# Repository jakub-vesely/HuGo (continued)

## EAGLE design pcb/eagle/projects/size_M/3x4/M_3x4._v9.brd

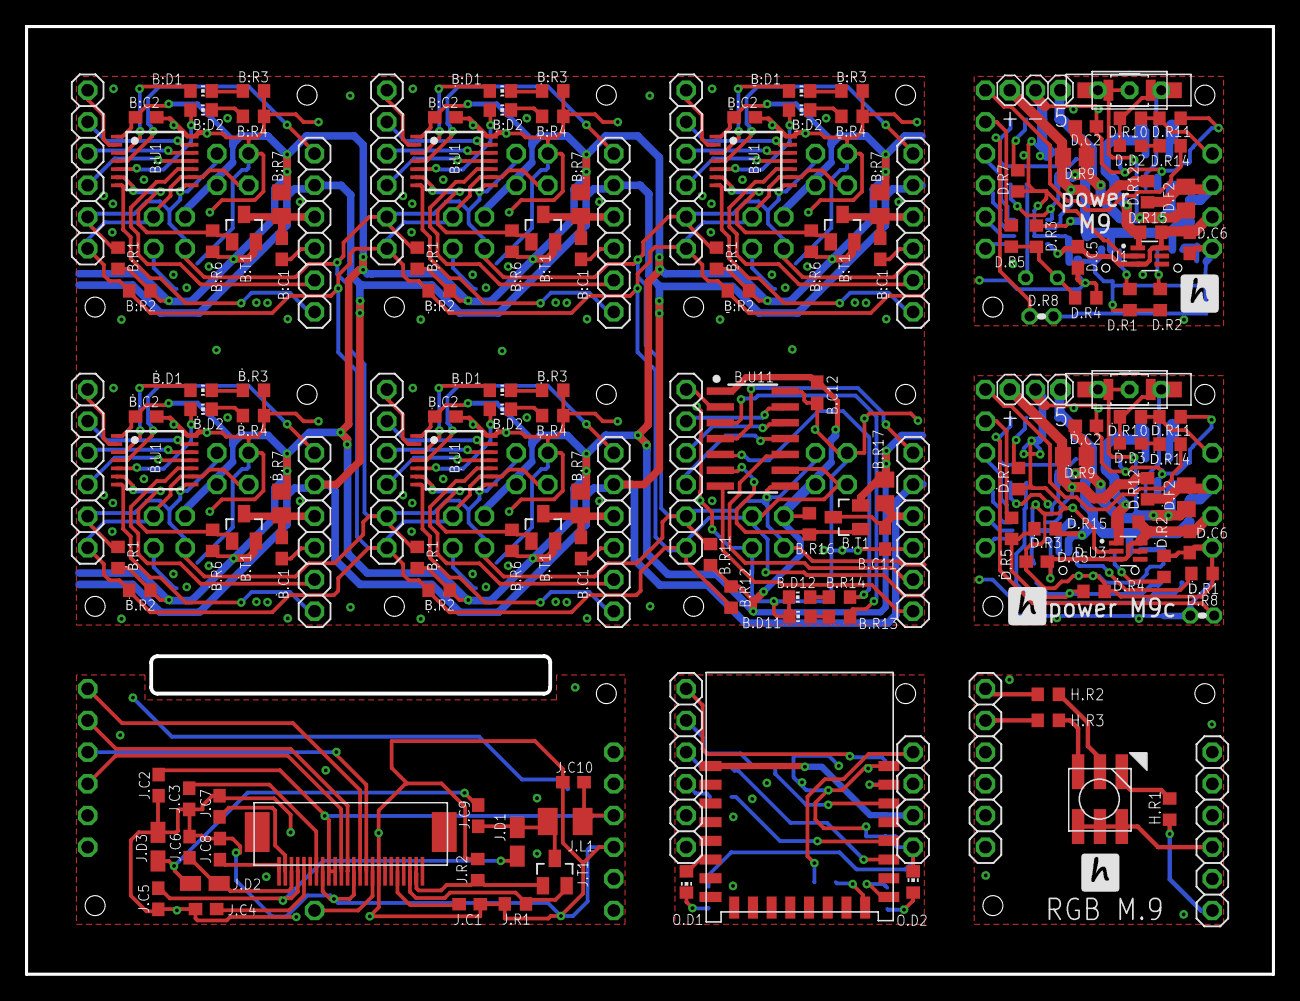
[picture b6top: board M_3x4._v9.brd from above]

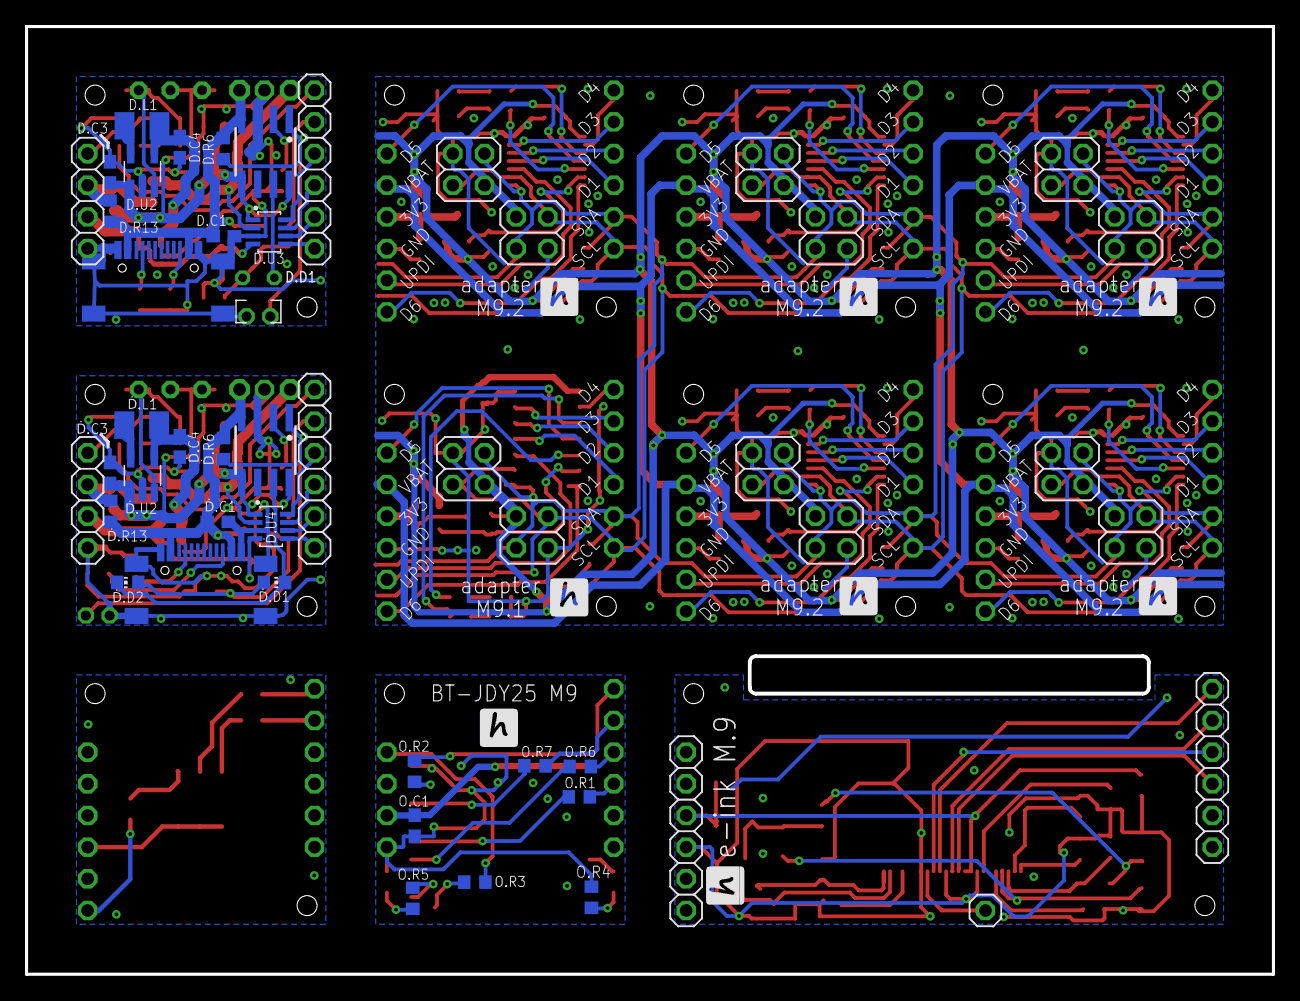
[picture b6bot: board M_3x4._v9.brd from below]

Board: 2 copper layers, 100.0 x 76.0 mm, 205 parts (50 on the bottom side), 170 nets.

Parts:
B.C11, B.C12: 100n; C0603
B.D11: RED; CHIP-LED0603
B.D12: GREEN; CHIP-LED0603
B.J1, B.J2, B.J5, B.J8, B.J9, B.J12, B.J13, B.J16, B.J17, B.J20, B.J21, B.J24: 1X06
B.J3, B.J4, B.J6, B.J7, B.J10, B.J11, B.J14, B.J15, B.J18, B.J19, B.J22, B.J23: 2X02
B.R11, B.R12, B.R14: 2k2; R0603
B.R13: 330; R0603
B.R16: 100k; R0603
B.R17: alt fuse or 0R; FUSE
B.T1: FDV304; SO23
B.U11: AT414; SO14
B:C1, B:C2: 100n; C0603
B:D1: RED; CHIP-LED0603
B:D2: GREEN; CHIP-LED0603
B:R1, B:R2, B:R4: 2k2; R0603
B:R3: 330; R0603
B:R6: 100k; R0603
B:R7: alt fuse or 0R; FUSE
B:T1: FDV304; SO23
B:U1: ATTINY3224-XU; TSSOP14
D.C1, D.C2, D.C3: 4u7; C0603
D.C4: 10u; C0603
D.C5, D.C6: 100n; C0603
D.D1: LED_1.8
D.D2: DIODE
D.F2: 1.1A; R0805
D.J2: 1X06
D.J3: 1X04
D.L1: 2u2; L3230M
D.LIPOL: PINHEAD-1X3-2; 1X-03-2
D.ON/OFF/RESET: SWITCH
D.R1, D.R2, D.R4: 5k1; R0603
D.R3: 3k3; R0603
D.R5, D.R6: 10k; R0603
D.R7: I=1800/R; R0603
D.R8: TERM_10K; THERM
D.R9: 0.1R; R0805
D.R10: 150k; R0603
D.R11: 330k; R0603
D.R12, D.R13: 0; R0603
D.R14: 680k; R0603
D.R15: 0R; R0603
D.U1: CN3083; SOP8
D.U2: LM3671_3.3; SOT32-5
D.U3: SOT23-8
G.J1: 1X06
G.J2: 1X04
H.D1: RGB_WW-FCE50TC-Q1
H.J1, H.J2: 1X06
H.R1, H.R2, H.R3: 82; R0603
J.C1, J.C4, J.C5, J.C6, J.C7, J.C9, J.C10: 4u7; C0603
J.C2, J.C3, J.C8: 1u; C0603
J.D1, J.D2, J.D3: SHOTKY_2.8
J.J1, J.J3: 1X06
J.J2: 1X01
J.J4: E-INK-24
J.L1: 10uH/1A; L3230M
J.R1: 82; R0603
J.R2: 100k; R0603
J.T1: NX3008; SO23
O.C1: 100n; C0603
O.D1, O.D2: CHIP-LED0603
O.R1, O.R2, O.R3, O.R4, O.R5, O.R6, O.R7: 2k2; R0603
U1: LM66100DCKR; SOT65P210X110-6N
U$1: USB-C
U$2: JDY-25
Ḃ.C1, Ḃ.C2: 100n; C0603
Ḃ.D1: RED; CHIP-LED0603
Ḃ.D2: GREEN; CHIP-LED0603
Ḃ.R1, Ḃ.R2, Ḃ.R4: 2k2; R0603
Ḃ.R3: 330; R0603
Ḃ.R6: 100k; R0603
Ḃ.R7: alt fuse or 0R; FUSE
Ḃ.T1: FDV304; SO23
Ḃ.U1: ATTINY3224-XU; TSSOP14
Ḅ.C1, Ḅ.C2: 100n; C0603
Ḅ.D1: RED; CHIP-LED0603
Ḅ.D2: GREEN; CHIP-LED0603
Ḅ.R1, Ḅ.R2, Ḅ.R4: 2k2; R0603
Ḅ.R3: 330; R0603
Ḅ.R6: 100k; R0603
Ḅ.R7: alt fuse or 0R; FUSE
Ḅ.T1: FDV304; SO23
Ḅ.U1: ATTINY3224-XU; TSSOP14
Ḅ:C1, Ḅ:C2: 100n; C0603
Ḅ:D1: RED; CHIP-LED0603
Ḅ:D2: GREEN; CHIP-LED0603
Ḅ:R1, Ḅ:R2, Ḅ:R4: 2k2; R0603
Ḅ:R3: 330; R0603
Ḅ:R6: 100k; R0603
Ḅ:R7: alt fuse or 0R; FUSE
Ḅ:T1: FDV304; SO23
Ḅ:U1: ATTINY3224-XU; TSSOP14
Ḇ:C1, Ḇ:C2: 100n; C0603
Ḇ:D1: RED; CHIP-LED0603
Ḇ:D2: GREEN; CHIP-LED0603
Ḇ:R1, Ḇ:R2, Ḇ:R4: 2k2; R0603
Ḇ:R3: 330; R0603
Ḇ:R6: 100k; R0603
Ḇ:R7: alt fuse or 0R; FUSE
Ḇ:T1: FDV304; SO23
Ḇ:U1: ATTINY3224-XU; TSSOP14
Ḋ.BTN: SWITCH
Ḋ.C1, Ḋ.C2, Ḋ.C3: 4u7; C0603
Ḋ.C4: 10u; C0603
Ḋ.C5, Ḋ.C6: 100n; C0603
Ḋ.D1, Ḋ.D2: CHIP-LED0603
Ḋ.D3: DIODE
Ḋ.F2: 1.1A; R0805
Ḋ.J1: USB-C
Ḋ.J2: 1X06
Ḋ.J3: 1X04
Ḋ.L1: 2u2; L3230M
Ḋ.LIPOL: PINHEAD-1X3-2; 1X-03-2
Ḋ.R1, Ḋ.R2, Ḋ.R4: 5k1; R0603
Ḋ.R3: 3k3; R0603
Ḋ.R5, Ḋ.R6, Ḋ.R14: 10k; R0603
Ḋ.R7: I=1800/R; R0603
Ḋ.R8: TERM_10K; THERM
Ḋ.R9: 0.1R; R0805
Ḋ.R10, Ḋ.R11: 100k; R0603
Ḋ.R12, Ḋ.R13: 0; R0603
Ḋ.R15: 0R; R0603
Ḋ.U1: CN3083; SOP8
Ḋ.U2: LM3671_3.3; SOT32-5
Ḋ.U3: LM66100DCKR; SOT65P210X110-6N
Ḋ.U4: SOT23-8

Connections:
5V: Ḋ.C1.2, Ḋ.J1.A4B9, Ḋ.J1.B4A9, Ḋ.LIPOL.1, Ḋ.R3.2, Ḋ.R6.2, Ḋ.R13.1, Ḋ.U1.4
5V1: D.C1.2, D.LIPOL.1, D.R3.2, D.R6.2, D.R13.1, D.U1.4, U$1.A4B9, U$1.B4A9
BUSY: J.J2.1, J.J4.P$9
CHRG: Ḋ.D1.A1, Ḋ.D2.A1, Ḋ.R3.1, Ḋ.R4.2, Ḋ.R5.1
CHRG1: D.D1.2, D.R3.1, D.R4.2, D.R5.1
D/C: J.J1.6, J.J4.P$11
GND: J.C1.2, J.C2.2, J.C3.2, J.C4.2, J.C5.2, J.C6.2, J.C7.2, J.C8.2, J.C10.2, J.D3.K, J.J3.4, J.J4.P$8, J.J4.P$12, J.J4.P$17, J.R1.2, J.R2.1
GND1: Ḋ.C1.1, Ḋ.C2.1, Ḋ.C3.1, Ḋ.C4.1, Ḋ.C5.1, Ḋ.C6.1, Ḋ.J1.A1B12, Ḋ.J1.B1A12, Ḋ.J1.SH1, Ḋ.J1.SH2, Ḋ.J1.SH3, Ḋ.J1.SH4, Ḋ.J3.4, Ḋ.LIPOL.2, Ḋ.R1.2, Ḋ.R2.2, Ḋ.R4.1, Ḋ.R7.1, Ḋ.R8.1, Ḋ.R11.2, Ḋ.U1.3, Ḋ.U2.GND, Ḋ.U3.2, Ḋ.U4.3
GND2: D.C1.1, D.C2.1, D.C3.1, D.C4.1, D.C5.1, D.C6.1, D.J3.4, D.LIPOL.2, D.R1.2, D.R2.2, D.R4.1, D.R7.1, D.R8.1, D.R11.2, D.U1.3, D.U2.GND, D.U3.3, U1.2, U$1.A1B12, U$1.B1A12, U$1.SH1, U$1.SH2, U$1.SH3, U$1.SH4
GND3: B.C11.2, B.C12.2, B.D11.C1, B.D12.C1, B.J3.4, B.J4.1, B.J5.4, B.J6.4, B.J7.1, B.J8.4, B.J10.4, B.J11.1, B.J12.4, B.J14.4, B.J15.1, B.J16.4, B.J18.4, B.J19.1, B.J20.4, B.J22.4, B.J23.1, B.J24.4, B.U11.14, B:C1.2, B:C2.2, B:R3.1, B:R4.1, B:U1.14, Ḃ.C1.2, Ḃ.C2.2, Ḃ.R3.1, Ḃ.R4.1, Ḃ.U1.14, Ḅ.C1.2, Ḅ.C2.2, Ḅ.R3.1, Ḅ.R4.1, Ḅ.U1.14, Ḅ:C1.2, Ḅ:C2.2, Ḅ:R3.1, Ḅ:R4.1, Ḅ:U1.14, Ḇ:C1.2, Ḇ:C2.2, Ḇ:R3.1, Ḇ:R4.1, Ḇ:U1.14
GND4: G.J2.4, O.C1.1, O.D2.C1, O.R4.1, U$2.GND
GND5: H.D1.4, H.D1.5, H.D1.6, H.J1.4
IN+: Ḋ.BTN.P$2, Ḋ.BTN.P$3, Ḋ.BTN.P$4, Ḋ.BTN.P$6, Ḋ.C2.2, Ḋ.C3.2, Ḋ.F2.1, Ḋ.R9.1, Ḋ.U1.5, Ḋ.U1.8, Ḋ.U2.VIN, Ḋ.U4.1
IN+1: D.C2.2, D.C3.2, D.F2.1, D.ON/OFF/RESET.P$2, D.ON/OFF/RESET.P$3, D.ON/OFF/RESET.P$4, D.ON/OFF/RESET.P$6, D.R9.1, D.U1.5, D.U1.8, D.U2.VIN, D.U3.1
IN-: Ḋ.LIPOL.3, Ḋ.R9.2, Ḋ.R12.1, Ḋ.U4.2
IN-1: D.LIPOL.3, D.R9.2, D.R12.1, D.U3.2
unnamed: Ḃ.D2.C1, Ḃ.R4.2
unnamed: Ḃ.D1.C1, Ḃ.R3.2
unnamed: B.J5.3, Ḃ.C1.1, Ḃ.R7.1, Ḃ.T1.D
unnamed: Ḅ.D1.A1, Ḅ.U1.3
unnamed: Ḃ.D1.A1, Ḃ.U1.3
unnamed: Ḅ.D2.C1, Ḅ.R4.2
unnamed: Ḅ.D1.C1, Ḅ.R3.2
unnamed: B.J8.3, Ḅ.C1.1, Ḅ.R7.1, Ḅ.T1.D
unnamed: Ḇ:D1.A1, Ḇ:U1.3
unnamed: Ḇ:D2.C1, Ḇ:R4.2
unnamed: Ḇ:D1.C1, Ḇ:R3.2
unnamed: B.J12.3, Ḇ:C1.1, Ḇ:R7.1, Ḇ:T1.D
unnamed: B:D1.A1, B:U1.3
unnamed: B:D2.C1, B:R4.2
unnamed: B:D1.C1, B:R3.2
unnamed: B.J16.3, B:C1.1, B:R7.1, B:T1.D
unnamed: Ḅ:D1.A1, Ḅ:U1.3
unnamed: Ḅ:D2.C1, Ḅ:R4.2
unnamed: Ḅ:D1.C1, Ḅ:R3.2
unnamed: B.J20.3, Ḅ:C1.1, Ḅ:R7.1, Ḅ:T1.D
unnamed: B.C11.1, B.J24.3, B.R17.1, B.T1.D
unnamed: B.D12.A1, B.R14.1
unnamed: B.R13.2, B.U11.3
unnamed: Ḋ.L1.1, Ḋ.U2.VOUT
unnamed: Ḋ.J1.B5, Ḋ.R1.1
unnamed: Ḋ.J1.A5, Ḋ.R2.1
unnamed: Ḋ.R7.2, Ḋ.U1.2
unnamed: Ḋ.D1.C1, Ḋ.D2.C1, Ḋ.U1.7
unnamed: Ḋ.R6.1, Ḋ.R8.2, Ḋ.U1.1
unnamed: Ḋ.BTN.P$1, Ḋ.BTN.P$5, Ḋ.BTN.P$7, Ḋ.D3.C, Ḋ.R10.1, Ḋ.U2.SHDN
unnamed: Ḋ.D3.A, Ḋ.R14.2
unnamed: D.L1.1, D.U2.VOUT
unnamed: D.R1.1, U$1.B5
unnamed: D.R2.1, U$1.A5
unnamed: D.R7.2, D.U1.2
unnamed: D.D1.1, D.U1.7
unnamed: D.R6.1, D.R8.2, D.U1.1
unnamed: D.D2.C, D.ON/OFF/RESET.P$1, D.ON/OFF/RESET.P$5, D.ON/OFF/RESET.P$7, D.R10.1, D.U2.SHDN
unnamed: D.D2.A, D.R14.2
unnamed: J.C1.1, J.J4.P$5
unnamed: J.C8.1, J.J4.P$24
unnamed: J.C6.1, J.D2.A, J.J4.P$22
unnamed: J.C3.1, J.J4.P$18
unnamed: J.C4.1, J.J4.P$20
unnamed: J.C2.1, J.C10.1, J.J3.3, J.J4.P$15, J.J4.P$16, J.L1.1
unnamed: J.C7.1, J.J4.P$23
unnamed: J.C9.1, J.D1.A, J.L1.2, J.T1.D
unnamed: J.C5.1, J.D1.K, J.J4.P$21
unnamed: J.J4.P$3, J.R1.1, J.T1.S
unnamed: J.J4.P$2, J.R2.2, J.T1.G
unnamed: J.C9.2, J.D2.K, J.D3.A
unnamed: G.J2.1, O.R3.2
unnamed: O.R1.1, U$2.RXD
unnamed: O.R6.1, U$2.TXD
unnamed: G.J1.5, O.R7.2
unnamed: O.R7.1, U$2.PWRC
unnamed: O.D2.A1, O.R5.1
unnamed: O.R5.2, U$2.ALED
unnamed: O.D1.A1, U$2.STAT
unnamed: O.D1.C1, O.R4.2
unnamed: O.R2.2, U$2.RST
unnamed: G.J1.6, O.R2.1
unnamed: O.R3.1, U$2.OUT1
unnamed: H.D1.2, H.R2.2
unnamed: H.D1.1, H.R1.2
unnamed: H.D1.3, H.R3.2
unnamed: H.J1.6, H.R1.1
unnamed: H.J2.6, H.R2.1
unnamed: H.J2.5, H.R3.1
PA1: B.J2.3, Ḃ.U1.11
PA2: B.J2.4, Ḃ.U1.12
PA3: B.J2.5, Ḃ.U1.13
PA4: B.J2.6, Ḃ.U1.2
PA5: B.J1.5, Ḅ.U1.13
PA6: B.J5.1, Ḃ.U1.4
PA7: Ḃ.D2.A1, Ḃ.U1.5
PA8: B.J1.4, Ḅ.U1.12
PA9: B.J1.6, Ḅ.U1.2
PA10: B.J1.3, Ḅ.U1.11
PA11: Ḅ.D2.A1, Ḅ.U1.5
PA12: B.J8.1, Ḅ.U1.4
PA13: B.J9.5, Ḇ:U1.13
PA14: B.J9.4, Ḇ:U1.12
PA15: B.J9.6, Ḇ:U1.2
PA16: B.J9.3, Ḇ:U1.11
PA17: Ḇ:D2.A1, Ḇ:U1.5
PA18: B.J12.1, Ḇ:U1.4
PA19: B.J13.5, B:U1.13
PA20: B.J13.4, B:U1.12
PA21: B.J13.6, B:U1.2
PA22: B.J13.3, B:U1.11
PA23: B:D2.A1, B:U1.5
PA24: B.J16.1, B:U1.4
PA25: B.J17.5, Ḅ:U1.13
PA26: B.J17.4, Ḅ:U1.12
PA27: B.J17.6, Ḅ:U1.2
PA28: B.J17.3, Ḅ:U1.11
PA29: Ḅ:D2.A1, Ḅ:U1.5
PA30: B.J20.1, Ḅ:U1.4
PA31: B.J21.5, B.U11.13
PA32: B.J21.4, B.U11.12
PA33: B.J21.6, B.U11.2
PA34: B.J21.3, B.U11.11
PA35: B.R14.2, B.U11.5
PA36: B.J24.1, B.U11.4
PA37: Ḋ.J2.4, Ḋ.U4.8
PA38: Ḋ.J2.3, Ḋ.U4.7
PA39: Ḋ.J2.5, Ḋ.R5.2
PA40: Ḋ.J2.6, Ḋ.R14.1
PA41: D.J2.4, D.U3.8
PA42: D.J2.3, D.U3.7
PA43: D.J2.5, D.R5.2
PA44: D.J2.6, D.R14.1
PA51: B.D11.A1, B.R13.1
PB1: Ḅ.R6.1, Ḅ.T1.G, Ḅ.U1.6
PB2: B.J5.6, Ḃ.U1.7
PB3: Ḃ.R6.1, Ḃ.T1.G, Ḃ.U1.6
PB4: B.J8.6, Ḅ.U1.7
PB5: Ḇ:R6.1, Ḇ:T1.G, Ḇ:U1.6
PB6: B.J12.6, Ḇ:U1.7
PB7: B:R6.1, B:T1.G, B:U1.6
PB8: B.J16.6, B:U1.7
PB9: Ḅ:R6.1, Ḅ:T1.G, Ḅ:U1.6
PB10: B.J20.6, Ḅ:U1.7
PB11: B.R16.1, B.T1.G, B.U11.6
PB12: B.J24.6, B.U11.7
PB13: Ḋ.J3.1, Ḋ.R10.2, Ḋ.R11.1
PB14: D.J3.1, D.R10.2, D.R11.1
RES: J.J1.4, J.J4.P$10
RX: G.J1.4, O.R6.2
SCL: B.J1.1, B.J2.1, B.J3.2, B.J4.3, B.J6.2, B.J7.3, B.J9.1, B.J10.2, B.J11.3, B.J13.1, B.J14.2, B.J15.3, B.J17.1, B.J18.2, B.J19.3, B.J21.1, B.J22.2, B.J23.3, B.R12.1, B.U11.9, B:R2.1, B:U1.9, Ḃ.R2.1, Ḃ.U1.9, Ḅ.R2.1, Ḅ.U1.9, Ḅ:R2.1, Ḅ:U1.9, Ḇ:R2.1, Ḇ:U1.9
SCL1: Ḋ.J2.1, Ḋ.U4.5
SCL2: D.J2.1, D.U3.5
SCLK: J.J1.5, J.J4.P$13
SDA: B.J1.2, B.J2.2, B.J3.3, B.J4.2, B.J6.3, B.J7.2, B.J9.2, B.J10.3, B.J11.2, B.J13.2, B.J14.3, B.J15.2, B.J17.2, B.J18.3, B.J19.2, B.J21.2, B.J22.3, B.J23.2, B.R11.1, B.U11.8, B:R1.1, B:U1.8, Ḃ.R1.1, Ḃ.U1.8, Ḅ.R1.1, Ḅ.U1.8, Ḅ:R1.1, Ḅ:U1.8, Ḇ:R1.1, Ḇ:U1.8
SDA1: Ḋ.J2.2, Ḋ.U4.6
SDA2: D.J2.2, D.U3.6
SDI: J.J1.3, J.J4.P$14
TX: G.J1.3, O.R1.2
UPDI: B.J5.5, Ḃ.U1.10
UPDI1: B.J8.5, Ḅ.U1.10
UPDI2: B.J12.5, Ḇ:U1.10
UPDI3: B.J16.5, B:U1.10
UPDI4: B.J20.5, Ḅ:U1.10
UPDI5: B.J24.5, B.U11.10
VBAT: B.J5.2, B.J8.2, B.J12.2, B.J16.2, B.J20.2, B.J24.2
VCC: B.C12.1, B.J3.1, B.J4.4, B.J6.1, B.J7.4, B.J10.1, B.J11.4, B.J14.1, B.J15.4, B.J18.1, B.J19.4, B.J22.1, B.J23.4, B.R11.2, B.R12.2, B.R16.2, B.R17.2, B.T1.S, B.U11.1, B:C2.1, B:R1.2, B:R2.2, B:R6.2, B:R7.2, B:T1.S, B:U1.1, Ḃ.C2.1, Ḃ.R1.2, Ḃ.R2.2, Ḃ.R6.2, Ḃ.R7.2, Ḃ.T1.S, Ḃ.U1.1, Ḅ.C2.1, Ḅ.R1.2, Ḅ.R2.2, Ḅ.R6.2, Ḅ.R7.2, Ḅ.T1.S, Ḅ.U1.1, Ḅ:C2.1, Ḅ:R1.2, Ḅ:R2.2, Ḅ:R6.2, Ḅ:R7.2, Ḅ:T1.S, Ḅ:U1.1, Ḇ:C2.1, Ḇ:R1.2, Ḇ:R2.2, Ḇ:R6.2, Ḇ:R7.2, Ḇ:T1.S, Ḇ:U1.1
VCC1: Ḋ.C4.2, Ḋ.L1.2, Ḋ.R15.2, Ḋ.U2.BP, Ḋ.U3.1
VCC2: Ḋ.C5.2, Ḋ.C6.2, Ḋ.J3.3, Ḋ.R15.1, Ḋ.U3.3, Ḋ.U3.6, Ḋ.U4.4
VCC3: D.C4.2, D.L1.2, D.R15.2, D.U2.BP, U1.1
VCC4: D.C5.2, D.C6.2, D.J3.3, D.R15.1, D.U3.4, U1.3, U1.6
VCC5: G.J2.3, O.C1.2, U$2.VCC
VOPT: Ḋ.F2.2, Ḋ.J3.2, Ḋ.R12.2, Ḋ.R13.2
VOPT1: D.F2.2, D.J3.2, D.R12.2, D.R13.2
